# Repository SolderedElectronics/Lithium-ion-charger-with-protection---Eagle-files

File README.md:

# Lithium-ion battery charger with protection - Eagle Files
## Image

[Lithium-ion battery charger with protection(222007)](https://e-radionica.com/hr/li-ion-punjac-s-zastitom-jst.html)

## Description and details
Since lithium batteries demand a special charging regime, and you must not charge them on a regular power source, you will need a charger like this one. Affordable, with integrated CC/CV charging regime, definitely the easiest way to charge some lithium batteries. Input voltage is connectable via USB cables or separate terminals. In addition, this charger includes battery protection which means that your cell (18650 battery for example) is protected from overvoltage, undervoltage and a large short circuit current.

- Input voltage: 4.5V-5.5V
- Output max. current: 1A, adjustable
- A voltage at which the charging stops: 4.2V
- Two LED diodes, red diode signals charging, green diode signals full battery
- With short circuit, overvoltage and undervoltage protection!
- Without reverse polarity protection on input!

## Repository content
This repo contains Cadsoft Eagle .sch and .brd files for Croduino Basic board. It also contains schematic in .pdf created from .sch Eagle file. 
Files have been arranged into folders for navigating between different versions of board. 
Tip: layer 200 shows top silkscreen and layer 208 should be bottom silkscreen. tParts and bParts is not used.

## Docs
- [Lithium-ion battery charger with protection] (https://e-radionica.com/hr/li-ion-punjac-s-zastitom-jst.html)

## Board versions
- v1.0 - inital version

## License info
This product is open-source. Yay!
For any tech questions, contact us at techsupport@e-radionica.com
If you find an Issue, please open one at GitHub. If you can improve our product, fork us.

e-radionica.com Team.

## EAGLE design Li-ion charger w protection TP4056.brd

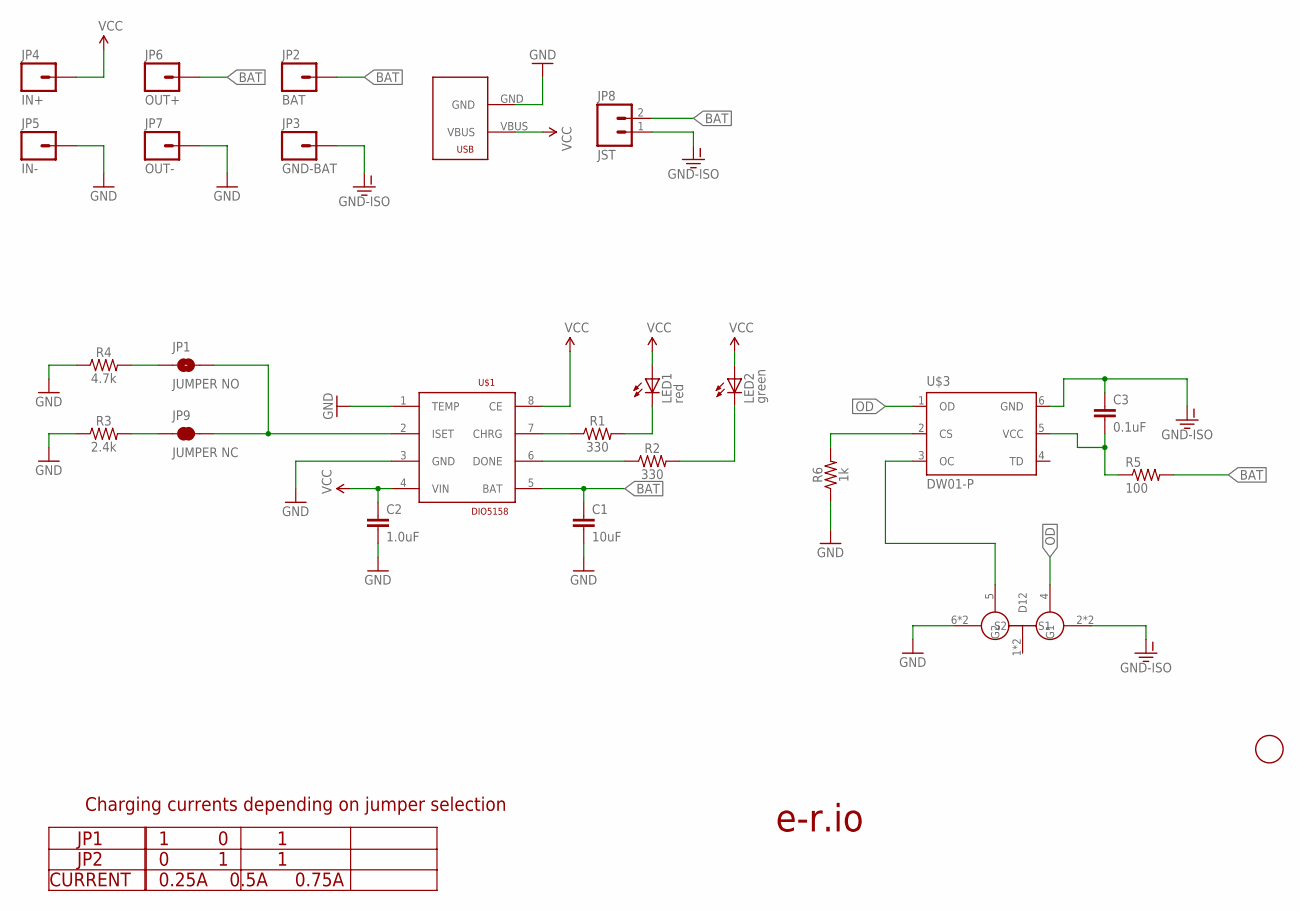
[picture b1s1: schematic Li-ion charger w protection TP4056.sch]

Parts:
C1: 10uF; 1206
C2: 1.0uF; 0603
C3: 0.1uF; 0603
JP1: JUMPER NO; SMT-JUMPER_2_NO_NO-SILK
JP2: BAT; 1X01
JP3: GND-BAT; 1X01
JP4: IN+; 1X01
JP5: IN-; 1X01
JP6: OUT+; 1X01
JP7: OUT-; 1X01
JP8: JST; JST-2-SMD
JP9: JUMPER NC; SMT-JUMPER_2_NC_TRACE_NO-SILK
LED1: red; CHIP-LED0805
LED2: green; CHIP-LED0805
R1, R2: 330; 0603
R3: 2.4k; 0603
R4: 4.7k; 0603
R5: 100; 0603-RES
R6: 1k; 0603
U$1: DIO5158; SOIC-8
U$2: FIDUCIAL; FIDUCIAL_1MM
U$3: DW01-P; SOT23-6L
U$4: FS8205A; TSSOP8
U$5: USB-MICROB-POWERONLY

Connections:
BAT: C1.1, JP2.1, JP6.1, JP8.2, R5.2, U$1.5 (BAT)
CHRG: R1.1, U$1.7 (CHRG)
DONE: R2.1, U$1.6 (DONE)
GND: C1.2, C2.2, JP5.1, JP7.1, R3.1, R4.1, R6.1, U$1.1 (TEMP), U$1.3 (GND), U$4.6 (S2), U$4.7 (S2), U$5.GND
GND-ISO: C3.1, JP3.1, JP8.1, U$3.6 (GND), U$4.2 (S1), U$4.3 (S1)
ISET: JP1.2, JP9.2, U$1.2 (ISET)
LED1: LED1.C, R1.2
LED2: LED2.C, R2.2
unnamed: R6.2, U$3.2 (CS)
unnamed: U$3.3 (OC), U$4.5 (G2)
unnamed: JP9.1, R3.2
unnamed: JP1.1, R4.2
OD: U$3.1 (OD), U$4.4 (G1)
VCC: C2.1, JP4.1, LED1.A, LED2.A, U$1.4 (VIN), U$1.8 (CE), U$5.VBUS
VCC-DW: C3.2, R5.1, U$3.5 (VCC)

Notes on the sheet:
JP1 JP2 CURRENT
1 0 1 0 1 1 0.25A 0.5A 0.75A
Charging currents depending on jumper selection
e-r.io

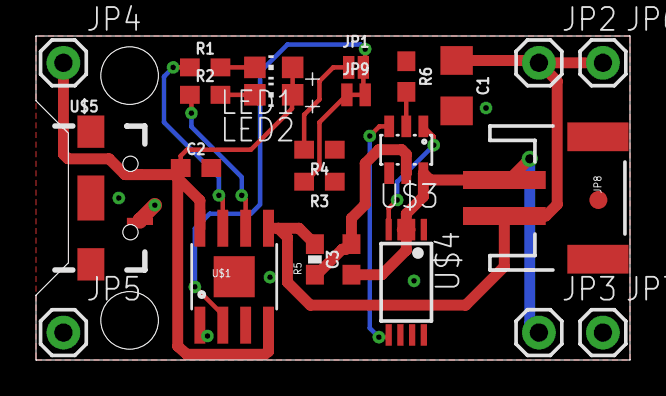
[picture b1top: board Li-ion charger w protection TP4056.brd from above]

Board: 2 copper layers, 33.0 x 18.0 mm, 30 parts (0 on the bottom side), 15 nets.

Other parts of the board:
U$6: LOGO-3MM
U$7: E-R.IO-3MM
U$8: OSH-3MM
U$9: LOGO-BACK-6MM
U$10: E-R.IO-BACK-6MM

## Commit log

2018-06-19 Initial
2018-11-26 README update

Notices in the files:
parts and their libraries:
SparkFun-Capacitors: Licensing: Creative Commons ShareAlike 4.0 International - https://creativecommons.org/licenses/by-sa/4.0
SparkFun: Licensing: CC v3.0 Share-Alike You are welcome to use this library for commercial purposes.
